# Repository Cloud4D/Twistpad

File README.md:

#  Twistpad
My submission for the Hack Club Hackpad project.

This repository contains all the files needed to produce a Twistpad, created by me. The Twistpad consists of a 3x3 grid of standard keys, which are bound to F13 - F21. On the right side of the grid, there are two dials, and the top one is bound to volume while the bottom one is bound to video controls (forward, backward, etc.). Additionally, there are LEDs, because who doesn't like a little RGB? I created this project over the course of nearly two weeks, using KiCad for the PCB, Fusion360 for the case design, and VSCode and Python for the firmware. 

So without further adieu, I present... the Twistpad!

## The hackpad:
A wonderful side view to give you an idea of the height

And then a top view so you can look through the window in the top right! (that tiny thing took me quite a long time)

The hackpad consists of a simple case design, with filleted corners and cutouts in the top to provide psace for the keys and dials to poke through. I wanted to add some extra stuff, so I spend time on the USB cutout (pictured below) making it look good and having it have a little inwards slant. i also spend time making the window into the PCB, which displays the Seeeduino logo perfectly. 

## Schematic of the PCB:
Made on KiCad, it was quite fun and easy to make it, no need to worry about physical space and stuff. 

The glorious PCB itself:
Also made on KiCad, it was also fun to do this, once I learned about vias. Has thicker traces for the 5V lines. 

## The case itself
This image pictures both the top plate and bottom part of the case, seperated. They fit together using M3x16mm screws along with M3x5mx4mm heatset inserts through the 4 holes on each corner of the case. In total, there are only 2 printed parts, the top and the bottom.

## The Firmware
This hackpad uses KMK firmware, and it was coded on VSCode using Python. 

## The BOM
1x Seeed XIAO RP2040

11x through-hold 1N4148 Diodes

9x MX-Style Switches

2x EC11 Rotary Encoders

9x white (or really any color or design you want) DSA keycaps

9x SK6812 MINI-E LEDs

4x M3x16mm screws

4x M3x5mx4mm heatset inserts

## Controls and binds
Imagine a 3x3 grid

A B C

D E F

G H I

Key A is bound to F13

Key B is bound to F14

Key C is bound to F15

Key D is bound to F16

Key E is bound to F17

Key F is bound to F18

Key G is bound to F19

Key H is bound to F20

Key I is bound to F21

In addition to that, due to a lack of pins, clicking down on the top dial is also mapped to whatever Key C is mapped to, and clicking down on the bottom dial is mapped to whatever Key I is mapped to.
Turning the top dial controls the volume, and turning the bottom dial controls video progress, like going forward in the video or backwards.

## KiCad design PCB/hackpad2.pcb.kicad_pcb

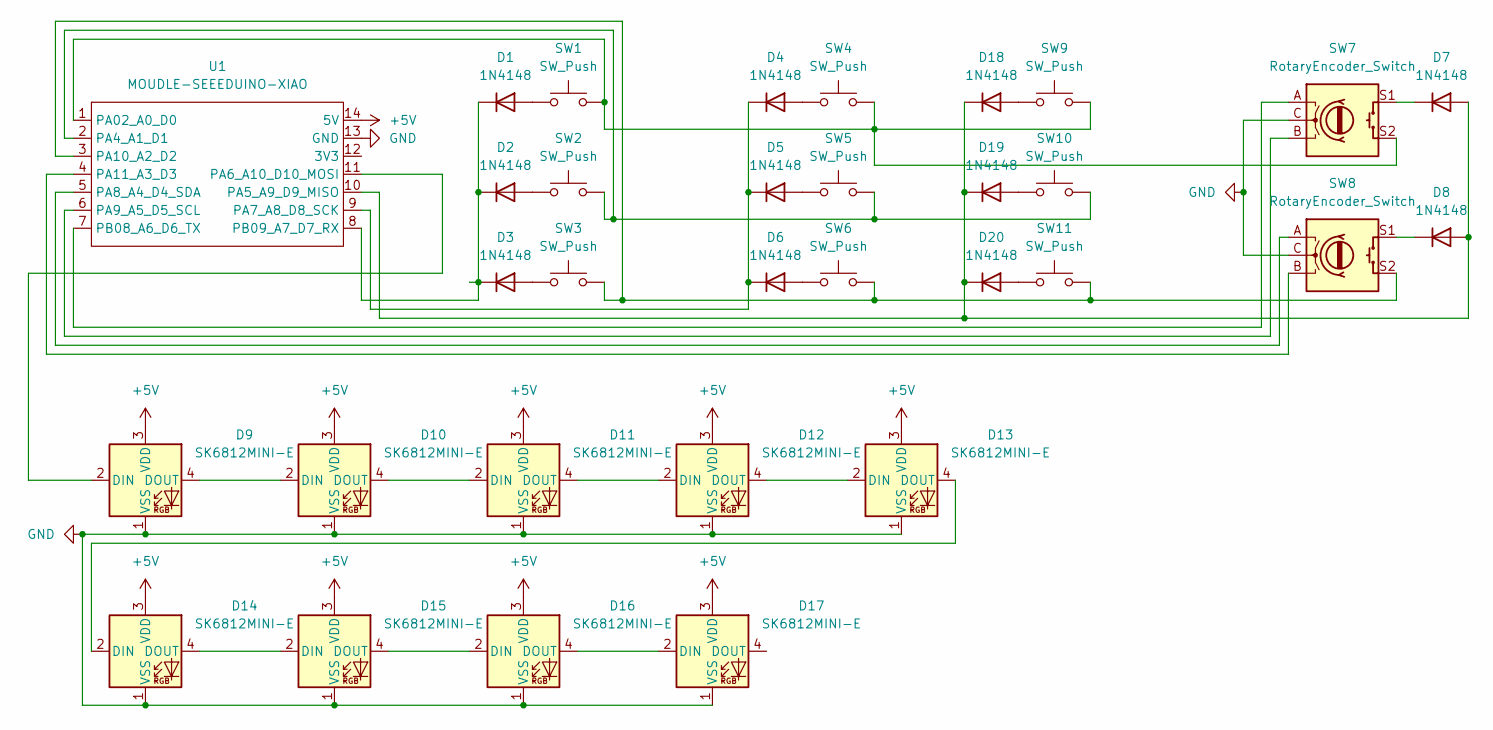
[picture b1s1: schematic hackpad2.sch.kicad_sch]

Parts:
D1, D2, D3, D4, D5, D6, D7, D8, D18, D19, D20: 1N4148; D_DO-35_SOD27_P7.62mm_Horizontal
D9, D10, D11, D12, D13, D14, D15, D16, D17: SK6812MINI-E; SK6812MINI-E_fixed
SW1, SW2, SW3, SW4, SW5, SW6, SW9, SW10, SW11: SW_Push; SW_Cherry_MX_1.00u_PCB
SW7, SW8: RotaryEncoder_Switch; RotaryEncoder_Alps_EC11E-Switch_Vertical_H20mm
U1: MOUDLE-SEEEDUINO-XIAO; XIAO-Generic-Hybrid-14P-2.54-21X17.8MM

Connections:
+5V: D9.3 (VDD), D10.3 (VDD), D11.3 (VDD), D12.3 (VDD), D13.3 (VDD), D14.3 (VDD), D15.3 (VDD), D16.3 (VDD), D17.3 (VDD), U1.14 (5V)
GND: D9.1 (VSS), D10.1 (VSS), D11.1 (VSS), D12.1 (VSS), D13.1 (VSS), D14.1 (VSS), D15.1 (VSS), D16.1 (VSS), D17.1 (VSS), SW7.C, SW8.C, U1.13 (GND)
unnamed: D1.2 (A), SW1.1
unnamed: D1.1 (K), D2.1 (K), D3.1 (K), U1.8 (PB09_A7_D7_RX)
unnamed: D2.2 (A), SW2.1
unnamed: D3.2 (A), SW3.1
unnamed: D4.2 (A), SW4.1
unnamed: D4.1 (K), D5.1 (K), D6.1 (K), U1.9 (PA7_A8_D8_SCK)
unnamed: D5.2 (A), SW5.1
unnamed: D6.2 (A), SW6.1
unnamed: D7.1 (K), SW7.S1
unnamed: D8.1 (K), SW8.S1
unnamed: D9.2 (DIN), U1.11 (PA6_A10_D10_MOSI)
unnamed: D9.4 (DOUT), D10.2 (DIN)
unnamed: D10.4 (DOUT), D11.2 (DIN)
unnamed: D11.4 (DOUT), D12.2 (DIN)
unnamed: D12.4 (DOUT), D13.2 (DIN)
unnamed: D13.4 (DOUT), D14.2 (DIN)
unnamed: D14.4 (DOUT), D15.2 (DIN)
unnamed: D15.4 (DOUT), D16.2 (DIN)
unnamed: D16.4 (DOUT), D17.2 (DIN)
unnamed: D18.2 (A), SW9.1
unnamed: D7.2 (A), D8.2 (A), D18.1 (K), D19.1 (K), D20.1 (K), U1.10 (PA5_A9_D9_MISO)
unnamed: D19.2 (A), SW10.1
unnamed: D20.2 (A), SW11.1
unnamed: SW1.2, SW4.2, SW7.S2, SW9.2, U1.1 (PA02_A0_D0)
unnamed: SW2.2, SW5.2, SW10.2, U1.2 (PA4_A1_D1)
unnamed: SW8.A, U1.5 (PA8_A4_D4_SDA)
unnamed: SW7.B, U1.6 (PA9_A5_D5_SCL)
unnamed: SW3.2, SW6.2, SW8.S2, SW11.2, U1.3 (PA10_A2_D2)
unnamed: SW8.B, U1.4 (PA11_A3_D3)
unnamed: SW7.A, U1.7 (PB08_A6_D6_TX)

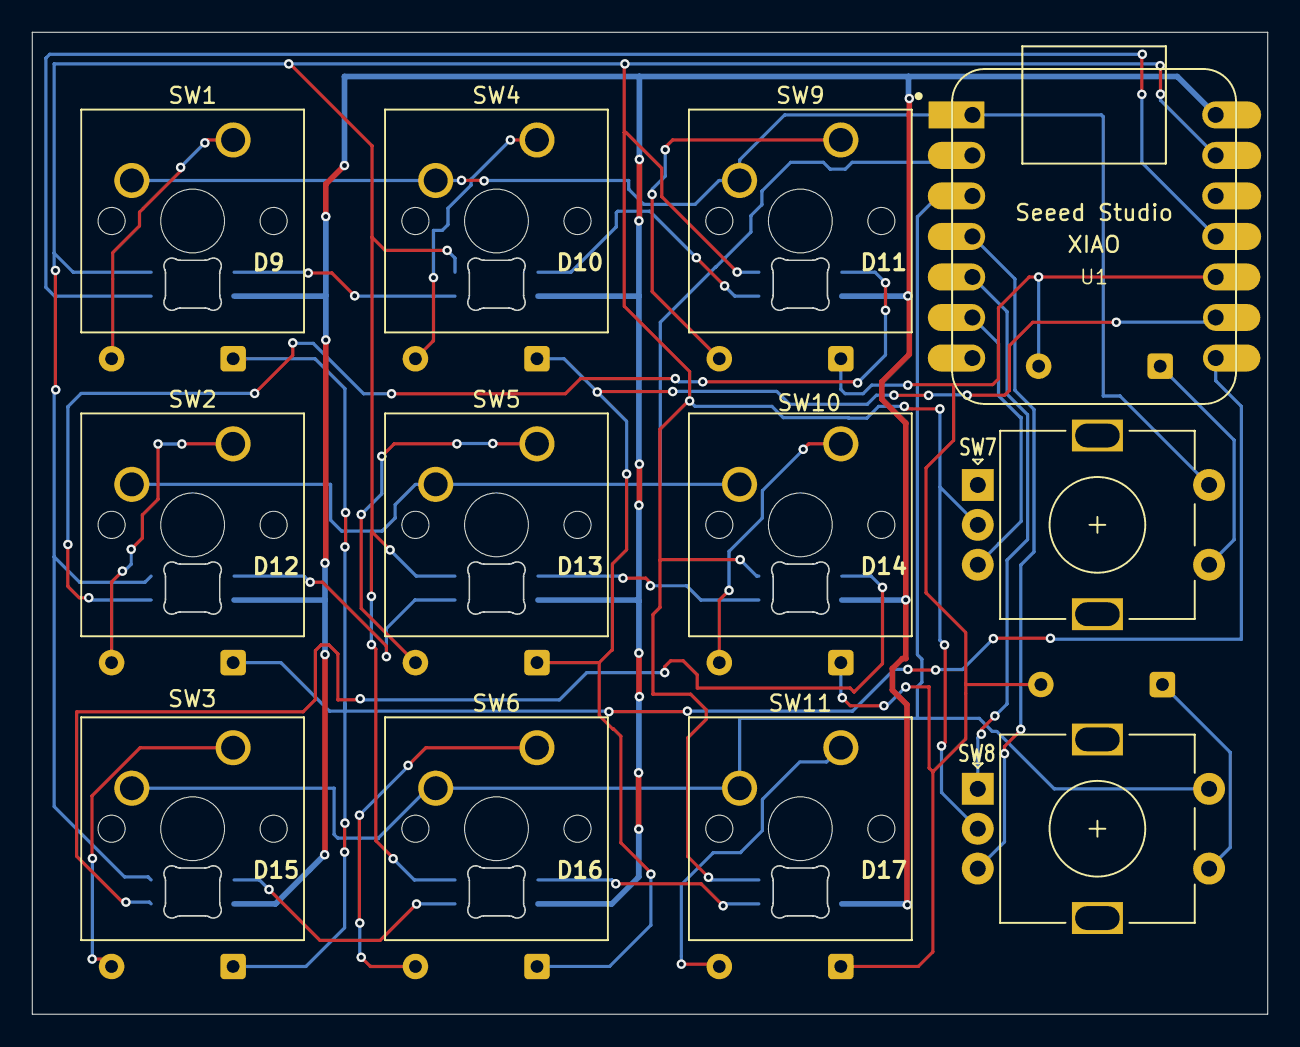
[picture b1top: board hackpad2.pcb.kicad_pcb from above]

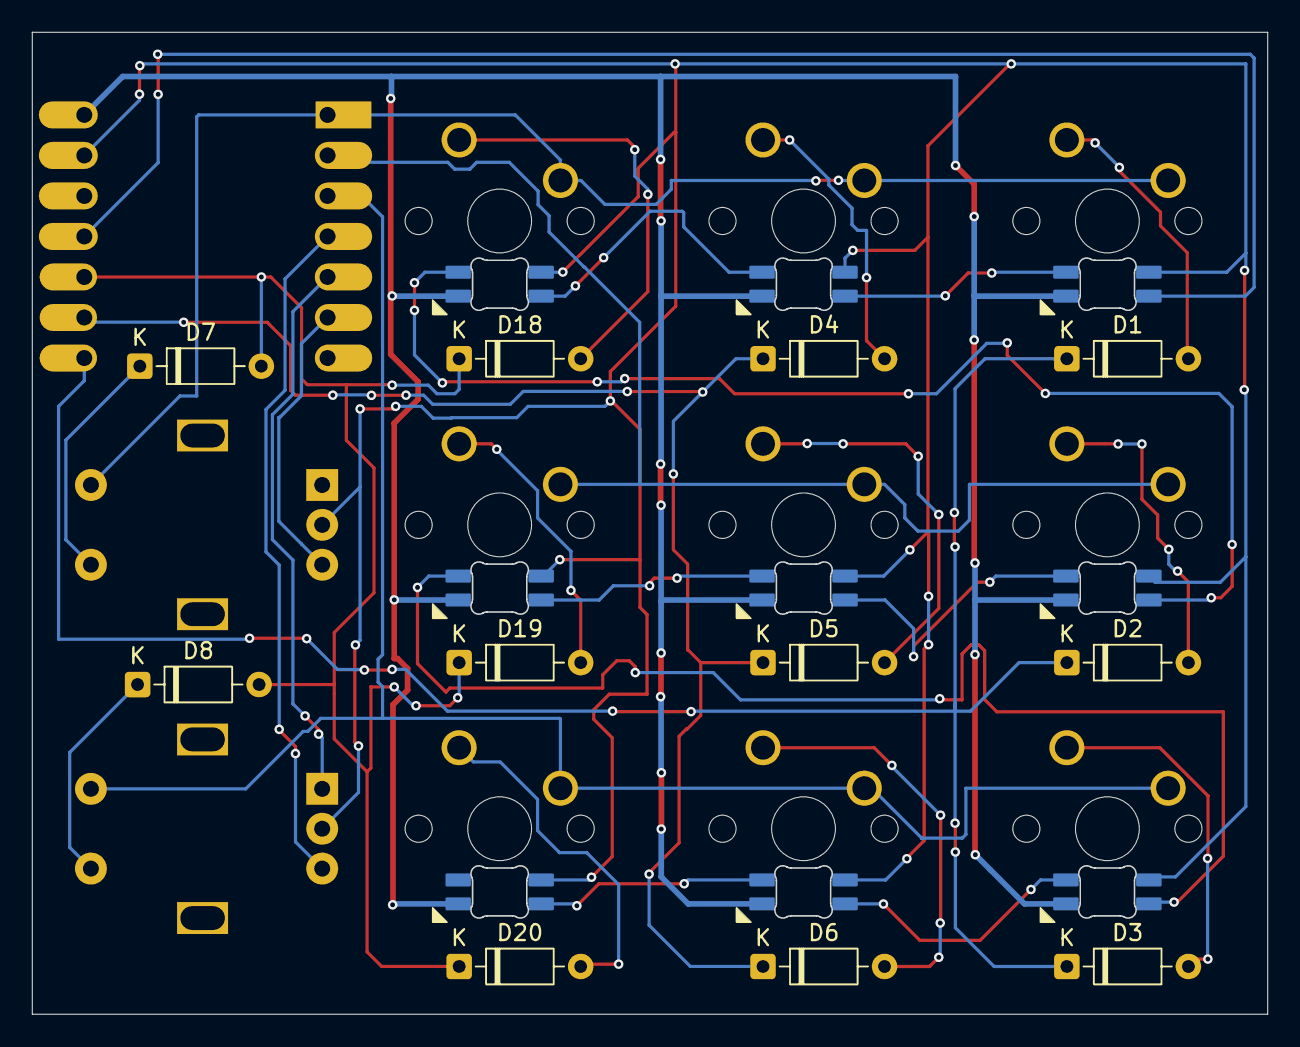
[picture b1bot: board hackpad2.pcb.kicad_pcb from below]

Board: 2 copper layers, 77.4 x 61.5 mm, 32 parts (11 on the bottom side), 32 nets.

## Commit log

2026-06-24 All of my files for this project
    Includes production files, PCB files, and firmware. CAD files would not fit, but the seperated files for the case are in the Production folder.
2026-06-24 Enhance README with project overview and images
    Expanded the README with project details, images, and descriptions.
2026-06-24 Enhance README with additional project details
    Added details about LEDs, case design, and BOM.
2026-06-25 Update README with firmware details and case description
    Added a new section about the firmware and clarified the case parts description.
2026-06-25 CAD Files
    Unfortunately the full CAD model is too big to fit in Github (over the 25mb limit) so I was forced to only send the top and bottom of the case.
